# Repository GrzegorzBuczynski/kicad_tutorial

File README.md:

https://www.youtube.com/watch?v=HkwVEqO4q_k&list=TLPQMzAxMjIwMjS4Qe-4bCJBsA&index=22

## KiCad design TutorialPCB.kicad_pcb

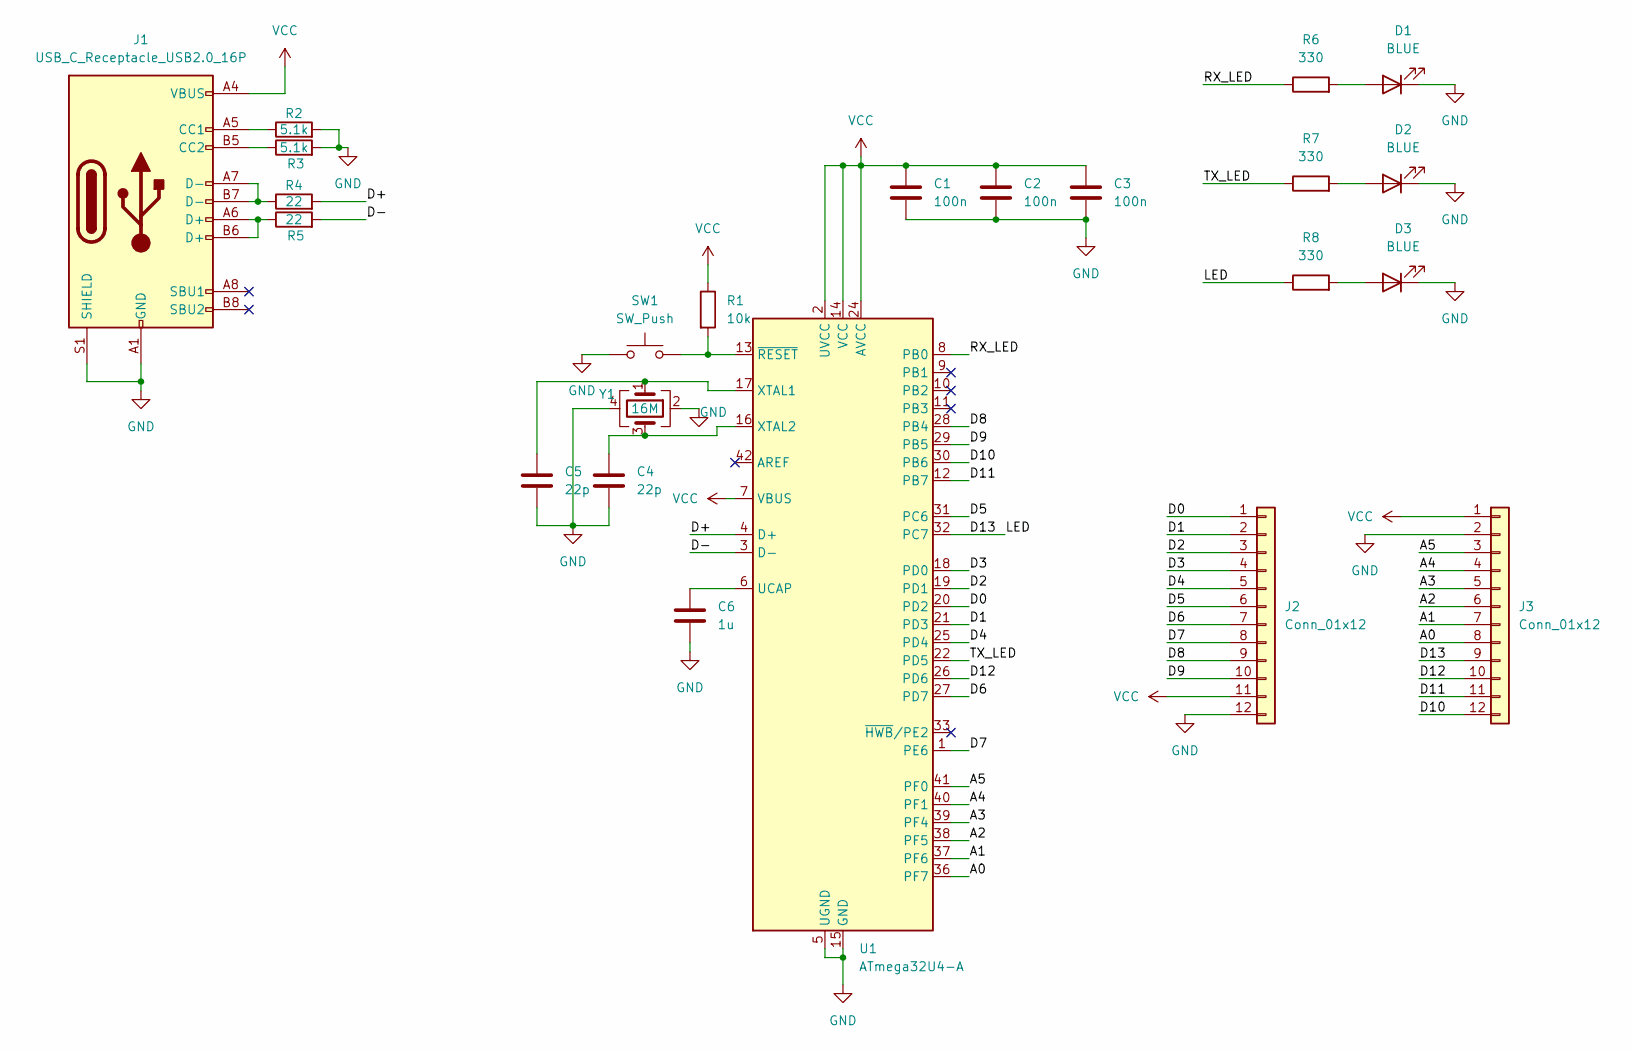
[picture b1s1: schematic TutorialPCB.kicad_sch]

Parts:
C1, C2, C3: 100n; C_0402_1005Metric_Pad0.74x0.62mm_HandSolder
C4, C5: 22p; C_0402_1005Metric
C6: 1u; C_0402_1005Metric
D1, D2, D3: BLUE; LED_0402_1005Metric
J1: USB_C_Receptacle_USB2.0_16P; USB_C_Receptacle_GCT_USB4105-xx-A_16P_TopMnt_Horizontal
J2, J3: Conn_01x12; PinHeader_1x12_P2.54mm_Vertical
R1: 10k; R_0402_1005Metric
R2, R3: 5.1k; R_0402_1005Metric_Pad0.72x0.64mm_HandSolder
R4, R5: 22; R_0402_1005Metric_Pad0.72x0.64mm_HandSolder
R6, R7, R8: 330; R_0402_1005Metric
SW1: SW_Push; SW_Push_1P1T_NO_CK_KMR2
U1: ATmega32U4-A; TQFP-44_10x10mm_P0.8mm
Y1: 16M; Crystal_SMD_2520-4Pin_2.5x2.0mm

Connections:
/A0: J3.8, U1.36 (PF7)
/A1: J3.7, U1.37 (PF6)
/A2: J3.6, U1.38 (PF5)
/A3: J3.5, U1.39 (PF4)
/A4: J3.4, U1.40 (PF1)
/A5: J3.3, U1.41 (PF0)
/D0: J2.1, U1.20 (PD2)
/D1: J2.2, U1.21 (PD3)
/D2: J2.3, U1.19 (PD1)
/D3: J2.4, U1.18 (PD0)
/D4: J2.5, U1.25 (PD4)
/D5: J2.6, U1.31 (PC6)
/D6: J2.7, U1.27 (PD7)
/D7: J2.8, U1.1 (PE6)
/D8: J2.9, U1.28 (PB4)
/D9: J2.10, U1.29 (PB5)
/D10: J3.12, U1.30 (PB6)
/D11: J3.11, U1.12 (PB7)
/D12: J3.10, U1.26 (PD6)
/D13: J3.9, R8.1, U1.32 (PC7)
/D+: R4.2, U1.4 (D+)
/D-: R5.2, U1.3 (D-)
/RX_LED: R6.1, U1.8 (PB0)
/TX_LED: R7.1, U1.22 (PD5)
GND: C1.2, C2.2, C3.2, C4.2, C5.2, C6.2, D1.1 (K), D2.1 (K), D3.1 (K), J1.A1 (GND), J1.A12 (GND), J1.B1 (GND), J1.B12 (GND), J1.S1 (SHIELD), J2.12, J3.2, R2.2, R3.2, SW1.1, U1.5 (UGND), U1.15 (GND), U1.23 (GND), U1.35 (GND), U1.43 (GND), Y1.2, Y1.4
unnamed: D1.2 (A), R6.2
unnamed: D2.2 (A), R7.2
unnamed: D3.2 (A), R8.2
unnamed: J1.A5 (CC1), R2.1
unnamed: J1.B5 (CC2), R3.1
unnamed: J1.A6 (D+), J1.B6 (D+), R5.1
unnamed: J1.A7 (D-), J1.B7 (D-), R4.1
unnamed: C6.1, U1.6 (UCAP)
unnamed: C5.1, U1.17 (XTAL1), Y1.1
unnamed: C4.1, U1.16 (XTAL2), Y1.3
unnamed: R1.2, SW1.2, U1.13 (~RESET)
VCC: C1.1, C2.1, C3.1, J1.A4 (VBUS), J1.A9 (VBUS), J1.B4 (VBUS), J1.B9 (VBUS), J2.11, J3.1, R1.1, U1.2 (UVCC), U1.7 (VBUS), U1.14 (VCC), U1.24 (AVCC), U1.34 (VCC), U1.44 (AVCC)

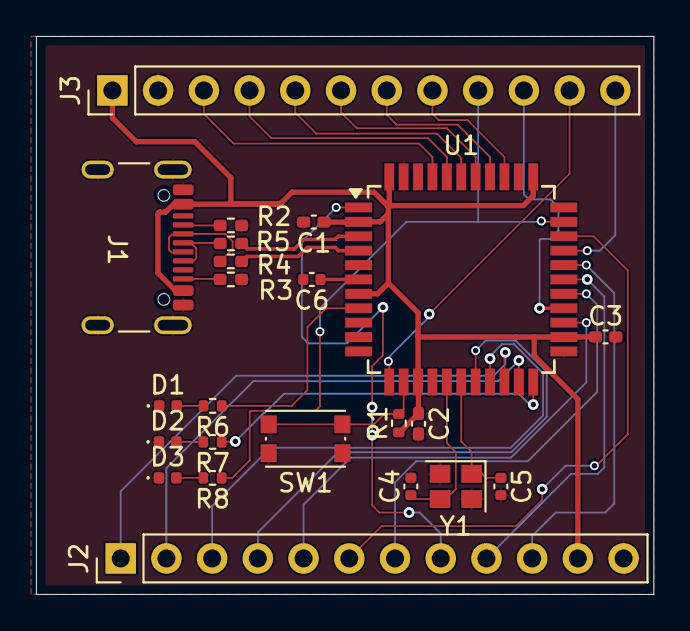
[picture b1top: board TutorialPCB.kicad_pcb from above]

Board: 2 copper layers, 34.3 x 31.0 mm, 23 parts (0 on the bottom side), 37 nets.

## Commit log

2025-01-15 first PCB
